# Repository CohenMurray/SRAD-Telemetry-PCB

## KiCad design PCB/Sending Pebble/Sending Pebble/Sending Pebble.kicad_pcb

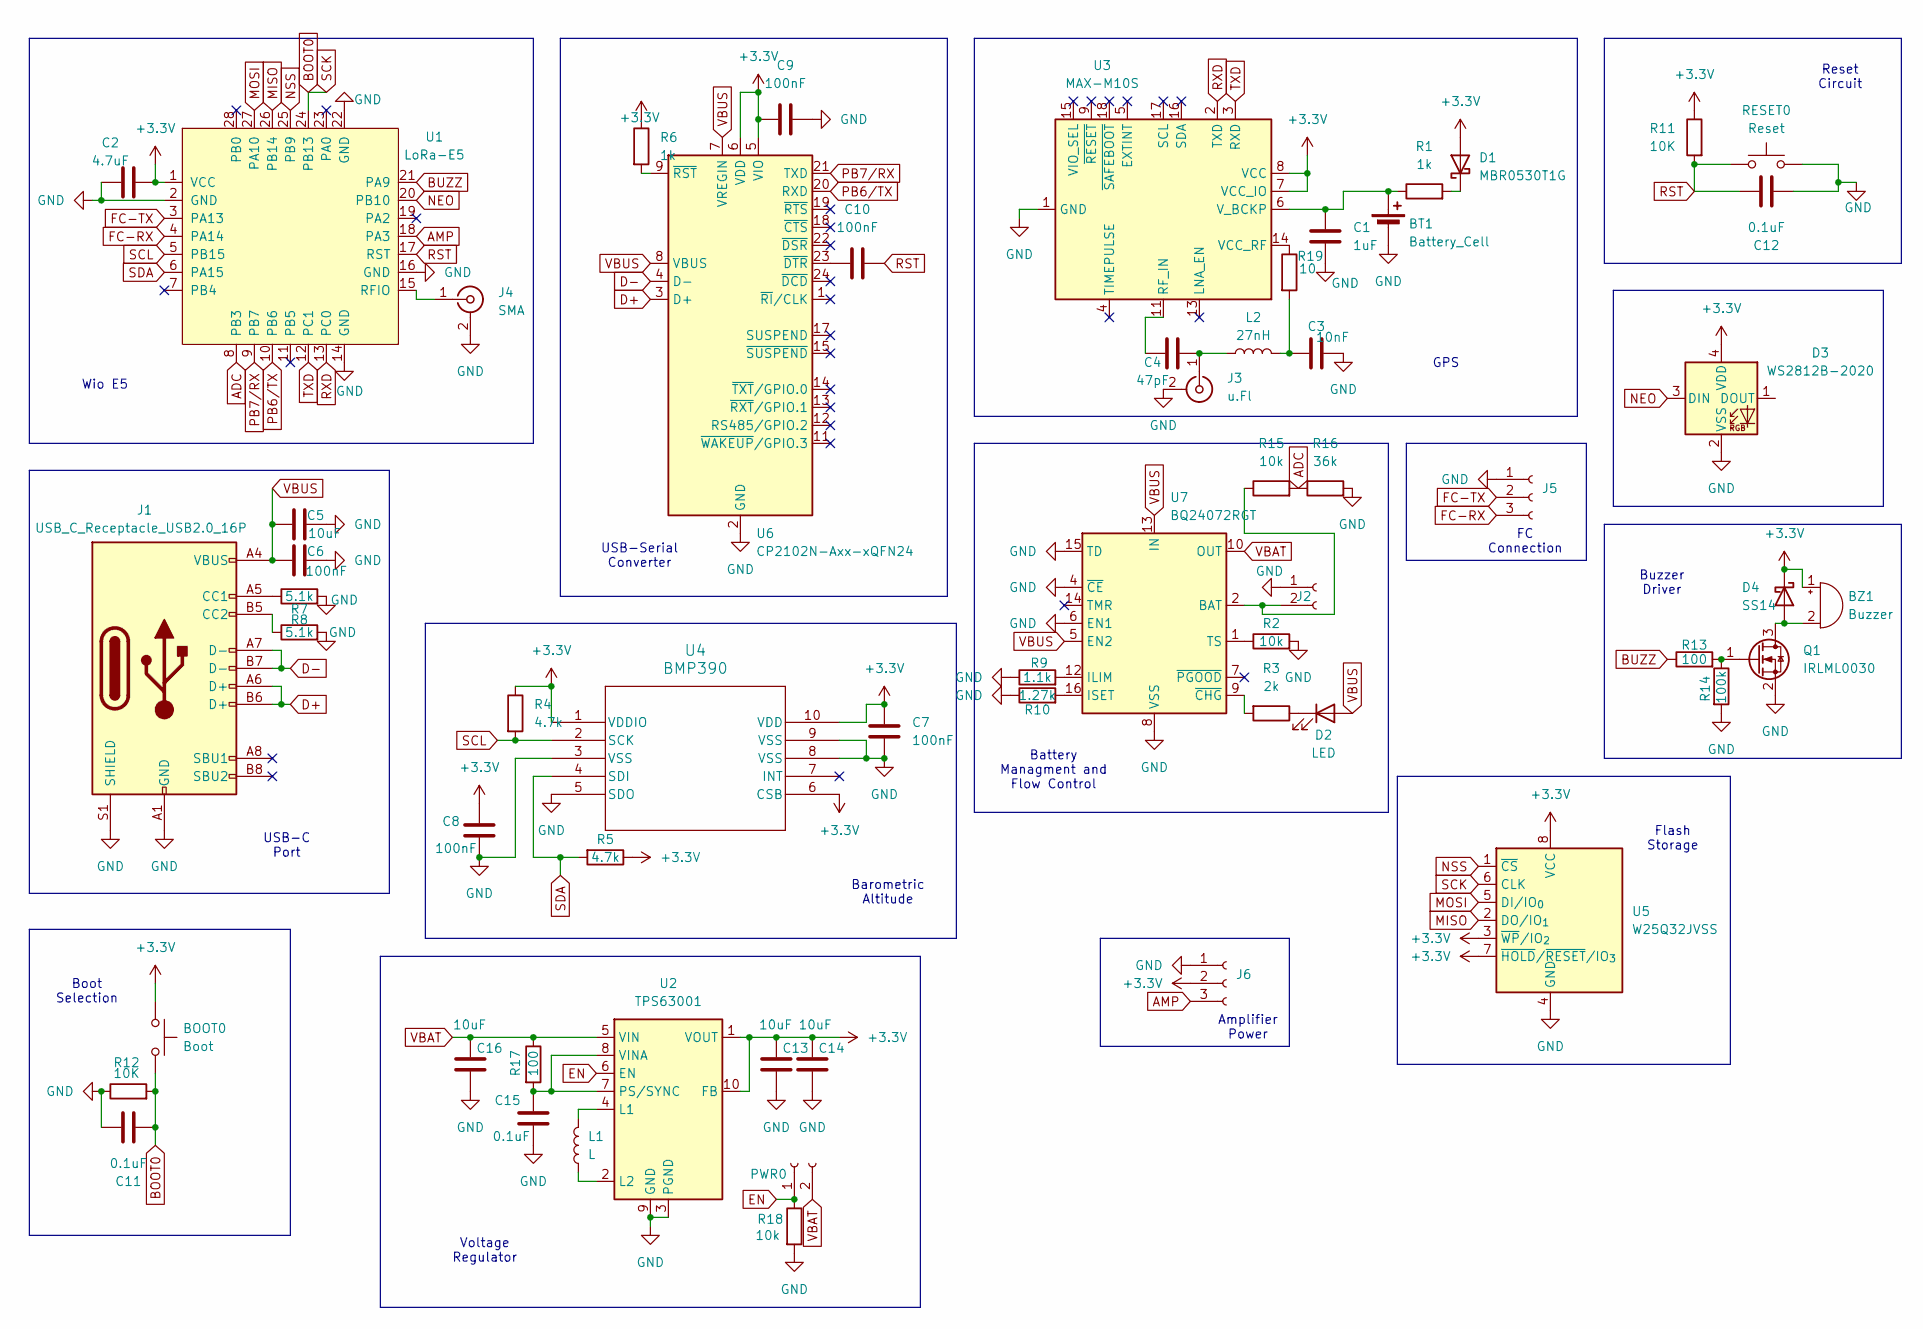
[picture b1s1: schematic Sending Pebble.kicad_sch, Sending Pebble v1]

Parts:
BOOT0: Boot; SW_SPST_PTS810
BT1: Battery_Cell; BatteryHolder_Seiko_MS621F
BZ1: Buzzer; MagneticBuzzer_PUI_SMT-1028-T-2-R
C1: 1uF; C_0603_1608Metric
C2: 4.7uF; C_0603_1608Metric
C3: 10nF; C_0402_1005Metric
C4: 47pF; C_0402_1005Metric
C5, C13, C14, C16: 10uF; C_0603_1608Metric
C6, C7, C8, C9, C10: 100nF; C_0603_1608Metric
C11, C12, C15: 0.1uF; C_0603_1608Metric
D1: MBR0530T1G; D_SOD-123
D2: LED; LED_0603_1608Metric
D3: WS2812B-2020; LED_WS2812B-2020_PLCC4_2.0x2.0mm
D4: SS14; D_SMA
J1: USB_C_Receptacle_USB2.0_16P; USB_C_Receptacle_HCTL_HC-TYPE-C-16P-01A
J2: Conn_01x02_Socket; JST_PH_S2B-PH-SM4-TB_1x02-1MP_P2.00mm_Horizontal
J3: u.Fl; U.FL_Hirose_U.FL-R-SMT-1_Vertical
J4: SMA; SMA_Amphenol_132289_EdgeMount
J5: Conn_01x03_Socket; JST_XH_B3B-XH-AM_1x03_P2.50mm_Vertical
J6: Conn_01x03_Socket; PinHeader_1x03_P2.54mm_Vertical
L1: L; IND_LQH3NPN2R2MMEL
L2: 27nH; C_0402_1005Metric
PWR0: Conn_01x02_Socket; PinSocket_1x02_P2.54mm_Vertical
Q1: IRLML0030; SOT-23
R1, R6: 1k; R_0603_1608Metric
R2, R15, R18: 10k; R_0603_1608Metric
R3: 2k; R_0603_1608Metric
R4, R5: 4.7k; R_0603_1608Metric
R7, R8: 5.1k; R_0603_1608Metric
R9: 1.1k; R_0603_1608Metric
R10: 1.27k; R_0603_1608Metric
R11, R12: 10K; R_0603_1608Metric
R13, R17: 100; R_0603_1608Metric
R14: 100k; R_0603_1608Metric
R16: 36k; R_0603_1608Metric
R19: 10; C_0402_1005Metric
RESET0: Reset; SW_SPST_PTS810
U1: LoRa-E5
U2: TPS63001; Texas_DRC0010J_ThermalVias
U3: MAX-M10S; ublox_MAX
U4: BMP390; 10LGA_2X2X0p75_BOS
U5: W25Q32JVSS; SOIC-8_5.3x5.3mm_P1.27mm
U6: CP2102N-Axx-xQFN24; QFN-24-1EP_4x4mm_P0.5mm_EP2.6x2.6mm
U7: BQ24072RGT; VQFN-16-1EP_3x3mm_P0.5mm_EP1.6x1.6mm

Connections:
+3.3V: BOOT0.1, BZ1.1 (+), C2.2, C7.1, C8.1, C9.1, C13.1, C14.1, D1.2 (A), D3.4 (VDD), D4.1 (K), J6.2, R4.1, R5.1, R6.1, R11.1, U1.1 (VCC), U2.1 (VOUT), U2.10 (FB), U3.7 (VCC_IO), U3.8 (VCC), U4.1 (VDDIO), U4.6 (CSB), U4.10 (VDD), U5.3 (~WP/IO_{2}), U5.7 (~HOLD/~RESET/IO_{3}), U5.8 (VCC), U6.5 (VIO), U6.6 (VDD)
ADC: R15.2, R16.1, U1.8 (PB3)
AMP: J6.3, U1.18 (PA3)
BOOT0: BOOT0.2, C11.2, R12.2, U1.24 (PB13~), U5.6 (CLK)
BUZZ: R13.1, U1.21 (PA9)
D+: J1.A6 (D+), J1.B6 (D+), U6.3 (D+)
D-: J1.A7 (D-), J1.B7 (D-), U6.4 (D-)
EN: PWR0.1, R18.1, U2.6 (EN)
FC-RX: J5.3, U1.4 (PA14)
FC-TX: J5.2, U1.3 (PA13)
GND: BT1.2 (-), C1.2, C2.1, C3.2, C5.2, C6.2, C7.2, C8.2, C9.2, C11.1, C12.2, C13.2, C14.2, C15.2, C16.2, D3.2 (VSS), J1.A1 (GND), J1.A12 (GND), J1.B1 (GND), J1.B12 (GND), J1.S1 (SHIELD), J2.1, J3.2 (Ext), J4.2 (Ext), J5.1, J6.1, Q1.2 (S), R2.2, R7.2, R8.2, R9.1, R10.1, R12.1, R14.2, R16.2, R18.2, RESET0.2, U1.2 (GND), U1.14 (GND), U1.16 (GND), U1.22 (GND), U2.3 (PGND), U2.9 (GND), U2.11 (PGND), U3.1 (GND), U3.10 (GND), U3.12 (GND), U4.3 (VSS), U4.5 (SDO), U4.8 (VSS), U4.9 (VSS), U5.4 (GND), U6.2 (GND), U6.25 (GND), U7.4 (~CE), U7.6 (EN1), U7.8 (VSS), U7.15 (TD), U7.17 (VSS)
MISO: U1.26 (PB14), U5.2 (DO/IO_{1})
MOSI: U1.27 (PA10), U5.5 (DI/IO_{0})
NEO: D3.3 (DIN), U1.20 (PB10)
NSS: U1.25 (PB9), U5.1 (~CS)
unnamed: BT1.1 (+), C1.1, R1.1, U3.6 (V_BCKP)
unnamed: BZ1.2 (-), D4.2 (A), Q1.3 (D)
unnamed: C3.1, L2.2, R19.2
unnamed: D1.1 (K), R1.2
unnamed: D2.1 (K), R3.1
unnamed: J1.A5 (CC1), R7.1
unnamed: J1.B5 (CC2), R8.1
unnamed: J2.2, R15.1, U7.2 (BAT), U7.3 (BAT)
unnamed: C4.2, J3.1 (In), L2.1
unnamed: J4.1 (In), U1.15 (RFIO)
unnamed: Q1.1 (G), R13.2, R14.1
unnamed: L1.2, U2.4 (L1)
unnamed: L1.1, U2.2 (L2)
unnamed: C15.1, R17.2, U2.7 (PS/SYNC), U2.8 (VINA)
unnamed: C4.1, U3.11 (RF_IN)
unnamed: R19.1, U3.14 (VCC_RF)
unnamed: C10.1, U6.23 (~DTR)
unnamed: R6.2, U6.9 (~RST)
unnamed: R9.2, U7.12 (ILIM)
unnamed: R10.2, U7.16 (ISET)
unnamed: R2.1, U7.1 (TS)
unnamed: R3.2, U7.9 (~CHG)
PB6/TX: U1.10 (PB6), U6.20 (RXD)
PB7/RX: U1.9 (PB7), U6.21 (TXD)
RST: C10.2, C12.1, R11.2, RESET0.1, U1.17 (RST)
RXD: U1.13 (PC0), U3.2 (TXD)
SCL: R4.2, U1.5 (PB15), U4.2 (SCK)
SDA: R5.2, U1.6 (PA15), U4.4 (SDI)
TXD: U1.12 (PC1), U3.3 (RXD)
VBAT: C16.1, PWR0.2, R17.1, U2.5 (VIN), U7.10 (OUT), U7.11 (OUT)
VBUS: C5.1, C6.1, D2.2 (A), J1.A4 (VBUS), J1.A9 (VBUS), J1.B4 (VBUS), J1.B9 (VBUS), U6.7 (VREGIN), U6.8 (VBUS), U7.5 (EN2), U7.13 (IN)

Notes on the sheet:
GPS
FC Connection
Battery Managment and Flow Control
USB-C Port
Flash Storage
Amplifier Power
Voltage Regulator
USB-Serial Converter
Barometric Altitude
Reset Circuit
Buzzer Driver
Wio E5
Boot Selection

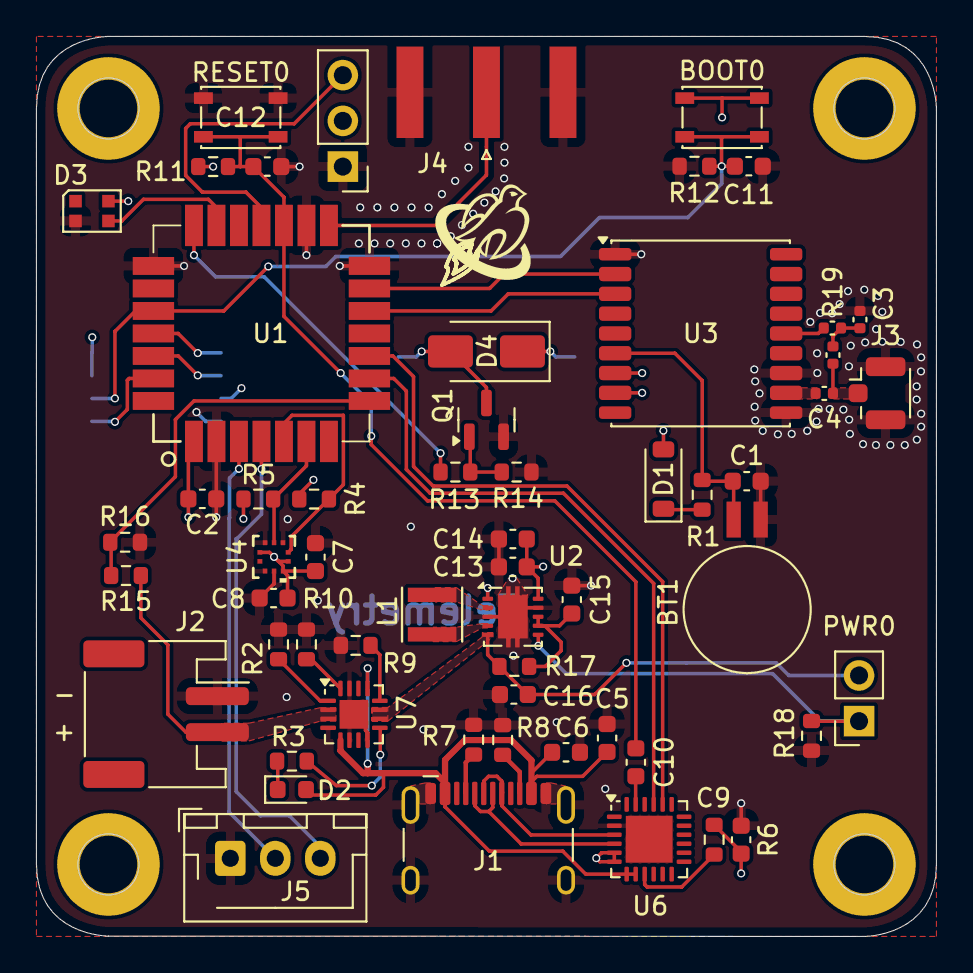
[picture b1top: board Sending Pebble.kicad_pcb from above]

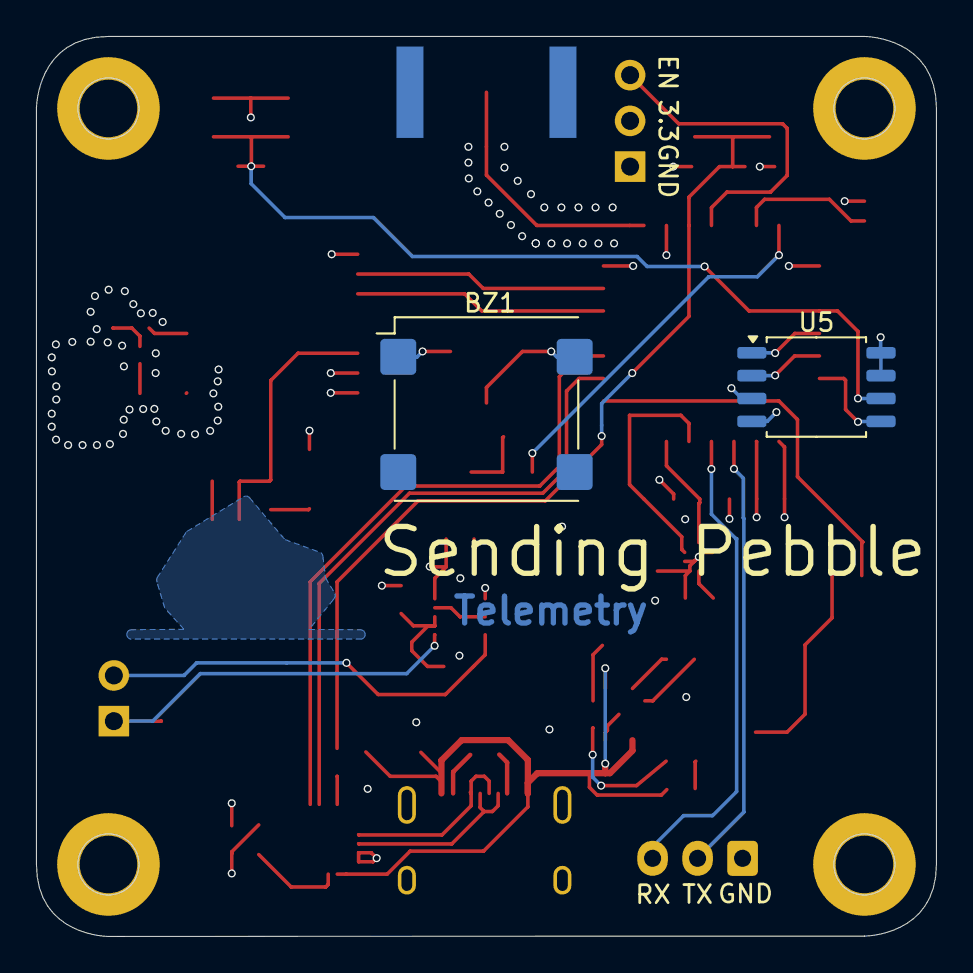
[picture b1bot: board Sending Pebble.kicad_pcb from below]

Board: 4 copper layers, 50.0 x 50.0 mm, 60 parts (2 on the bottom side), 46 nets.

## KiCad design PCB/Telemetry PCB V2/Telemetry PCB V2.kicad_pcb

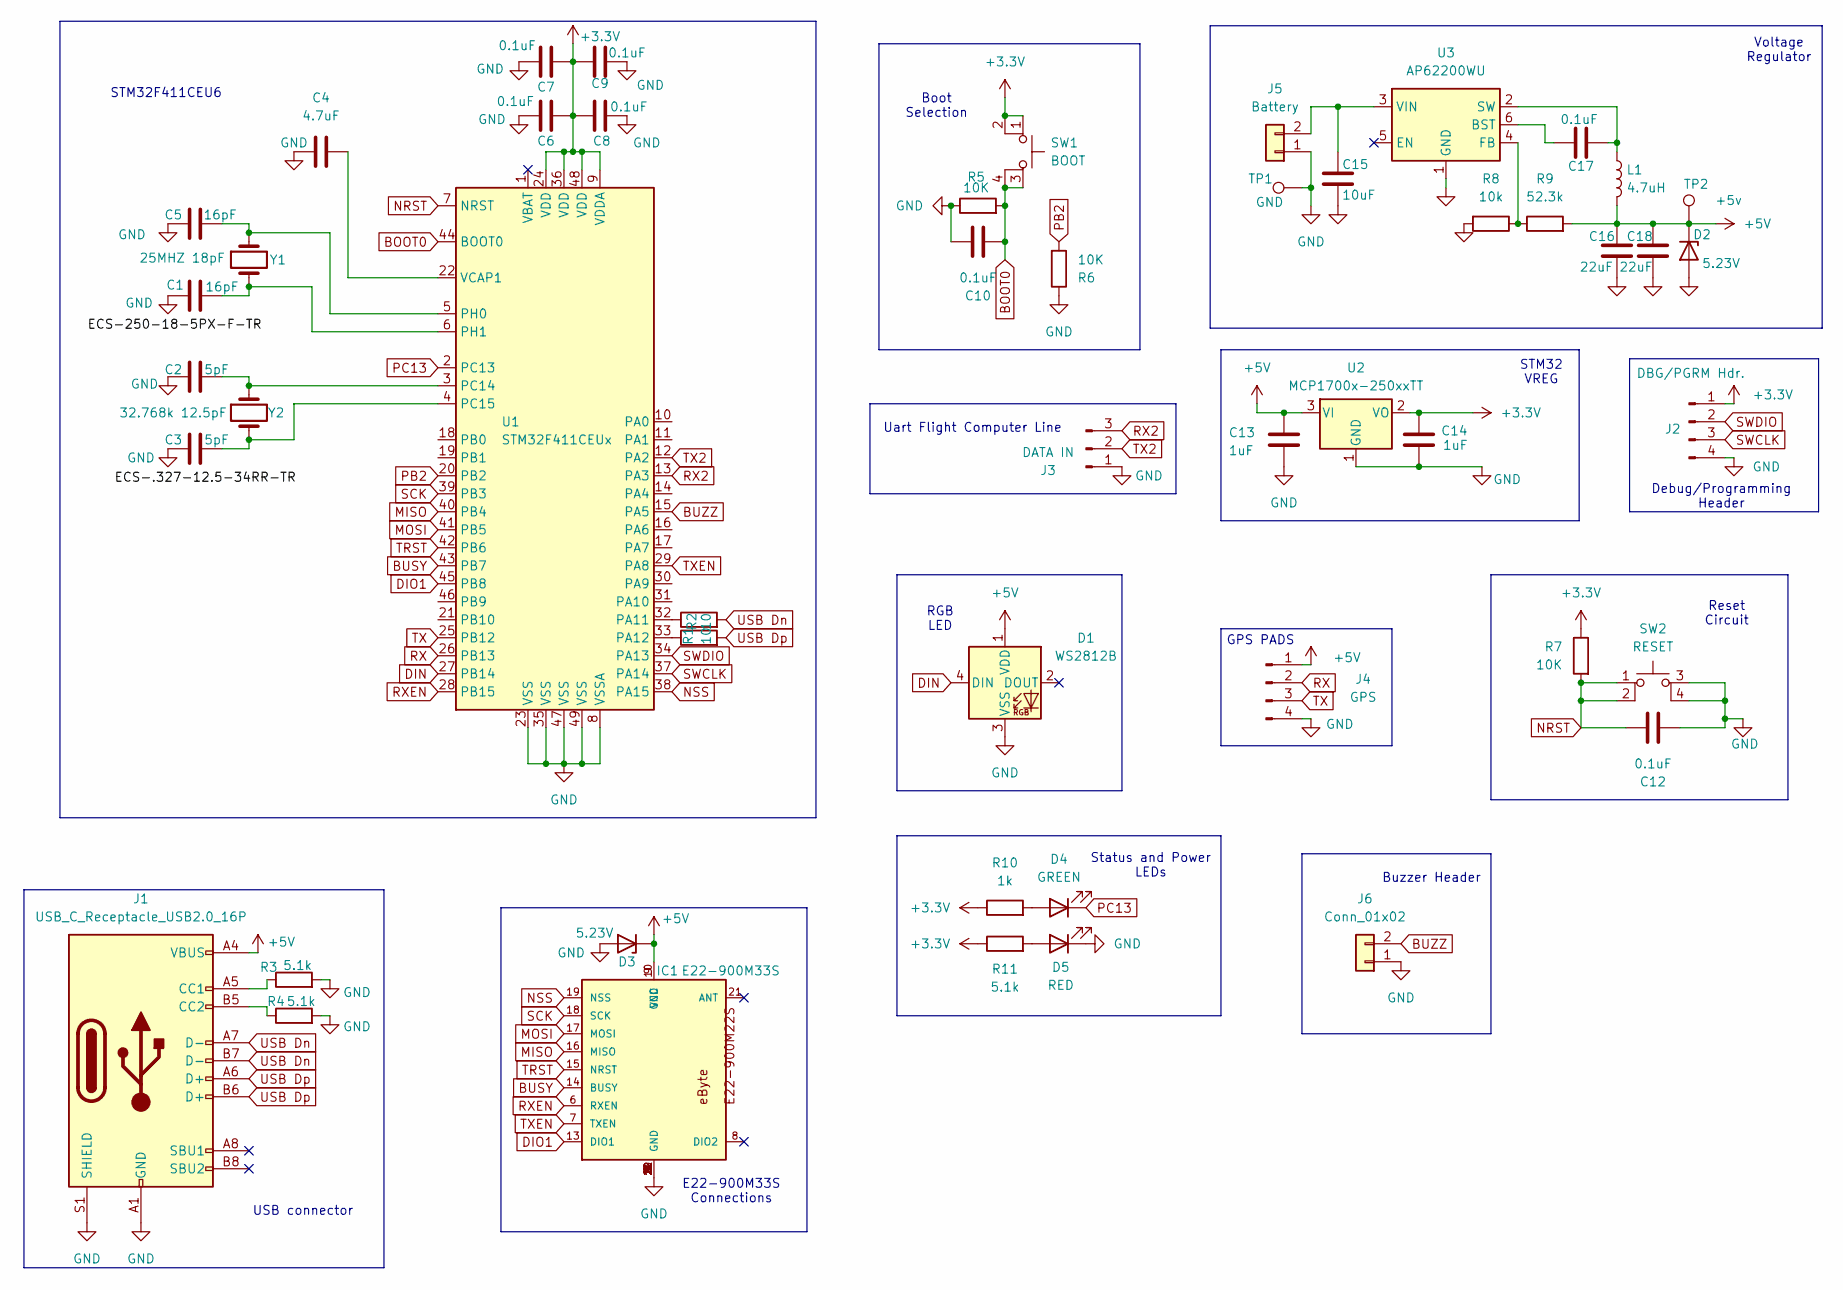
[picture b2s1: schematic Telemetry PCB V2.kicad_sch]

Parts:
C1, C5: 16pF; C_1206_3216Metric_Pad1.33x1.80mm_HandSolder
C2, C3: 5pF; C_0603_1608Metric_Pad1.08x0.95mm_HandSolder
C4: 4.7uF; C_1206_3216Metric_Pad1.33x1.80mm_HandSolder
C6, C7, C8, C9: 0.1uF; C_0603_1608Metric_Pad1.08x0.95mm_HandSolder
C10, C12, C17: 0.1uF; C_1206_3216Metric_Pad1.33x1.80mm_HandSolder
C13, C14: 1uF; C_1206_3216Metric_Pad1.33x1.80mm_HandSolder
C15: 10uF; C_1206_3216Metric_Pad1.33x1.80mm_HandSolder
C16, C18: 22uF; C_1206_3216Metric_Pad1.33x1.80mm_HandSolder
D1: WS2812B; LED_WS2812B_PLCC4_5.0x5.0mm_P3.2mm
D2, D3: 5.23V; CR_1C-G3&slash_H_VIS
D4: GREEN; LED_1206_3216Metric
D5: RED; LED_1206_3216Metric
IC1: E22-900M33S; XCVR_E22-900M33S
J1: USB_C_Receptacle_USB2.0_16P; USB_C_Receptacle_HCTL_HC-TYPE-C-16P-01A (SMALLER PADS)
J2: DBG/PGRM Hdr.; PinHeader_1x04_P2.54mm_Vertical
J3: DATA IN; JST_XH_B3B-XH-A_1x03_P2.50mm_Vertical
J4: GPS; PinHeader_1x04_P2.54mm_Vertical
J5: Battery; JST_XH_B2B-XH-A_1x02_P2.50mm_Vertical
J6: Conn_01x02; JST_XH_B2B-XH-A_1x02_P2.50mm_Vertical
L1: 4.7uH; IND_SRN5040_BRN
R1, R2: 10; C_1206_3216Metric_Pad1.33x1.80mm_HandSolder
R3, R4: 5.1k; C_1206_3216Metric_Pad1.33x1.80mm_HandSolder
R5, R6, R7: 10K; R_1206_3216Metric_Pad1.30x1.75mm_HandSolder
R8: 10k; R_1206_3216Metric_Pad1.30x1.75mm_HandSolder
R9: 52.3k; R_1206_3216Metric_Pad1.30x1.75mm_HandSolder
R10: 1k; R_1206_3216Metric
R11: 5.1k; R_1206_3216Metric
SW1: BOOT; SON4_PTS526 SM15 SMTR2 LFS_CNK
SW2: RESET; SON4_PTS526 SM15 SMTR2 LFS_CNK
TP1: GND; TestPoint_Loop_D1.80mm_Drill1.0mm_Beaded
TP2: +5v; TestPoint_Loop_D1.80mm_Drill1.0mm_Beaded
U1: STM32F411CEUx; QFN-48-1EP_7x7mm_P0.5mm_EP5.6x5.6mm
U2: MCP1700x-250xxTT; SOT-23
U3: AP62200WU; TSOT-23-6
Y1: 25MHZ 18pF; Crystal_SMD_HC49-SD_HandSoldering
Y2: 32.768k 12.5pF; XTAL_ECS-.327-12.5-34RR-TR

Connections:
+3.3V: C6.2, C7.1, C8.1, C9.2, C14.1, J2.1, R7.1, R10.1, R11.1, SW1.1, SW1.2, U1.9 (VDDA), U1.24 (VDD), U1.36 (VDD), U1.48 (VDD), U2.2 (VO)
+5V: C13.1, C16.2, C18.2, D1.1 (VDD), D2.1 (K), D3.1 (K), IC1.9 (VCC), IC1.10 (GND), J1.A4 (VBUS), J1.A9 (VBUS), J1.B4 (VBUS), J1.B9 (VBUS), J4.1, L1.2, R9.2, TP2.1, U2.3 (VI)
BOOT0: C10.2, R5.2, SW1.3 (A), SW1.4 (K), U1.44 (BOOT0)
BUSY: IC1.14 (BUSY), U1.43 (PB7)
BUZZ: J6.2, U1.15 (PA5)
DIN: D1.4 (DIN), U1.27 (PB14)
DIO1: IC1.13 (DIO1), U1.45 (PB8)
GND: C1.1, C2.1, C3.2, C4.1, C5.1, C6.1, C7.2, C8.2, C9.1, C10.1, C12.2, C13.2, C14.2, C15.2, C16.1, C18.1, D1.3 (VSS), D2.2 (A), D3.2 (A), D5.1 (K), IC1.1 (GND), IC1.2 (GND), IC1.3 (GND), IC1.4 (GND), IC1.5 (GND), IC1.11 (GND), IC1.12 (GND), IC1.20 (GND), IC1.22 (GND), J1.A1 (GND), J1.A12 (GND), J1.B1 (GND), J1.B12 (GND), J1.S1 (SHIELD), J2.4, J3.1, J4.4, J5.1, J6.1, R3.2, R4.2, R5.1, R6.1, R8.2, SW2.3 (A), SW2.4 (K), TP1.1, U1.8 (VSSA), U1.23 (VSS), U1.35 (VSS), U1.47 (VSS), U1.49 (VSS), U2.1 (GND), U3.1 (GND)
MISO: IC1.16 (MISO), U1.40 (PB4)
MOSI: IC1.17 (MOSI), U1.41 (PB5)
NRST: C12.1, R7.2, SW2.1, SW2.2, U1.7 (NRST)
NSS: IC1.19 (NSS), U1.38 (PA15)
unnamed: D4.2 (A), R10.2
unnamed: D5.2 (A), R11.2
unnamed: J1.A5 (CC1), R3.1
unnamed: J1.B5 (CC2), R4.1
unnamed: C15.1, J5.2, U3.3 (VIN)
unnamed: R1.1, U1.32 (PA11)
unnamed: R2.1, U1.33 (PA12)
unnamed: C2.2, U1.3 (PC14), Y2.1
unnamed: C3.1, U1.4 (PC15), Y2.2
unnamed: C5.2, U1.5 (PH0), Y1.1
unnamed: C1.2, U1.6 (PH1), Y1.2
unnamed: C4.2, U1.22 (VCAP1)
unnamed: C17.1, U3.6 (BST)
unnamed: R8.1, R9.1, U3.4 (FB)
unnamed: C17.2, L1.1, U3.2 (SW)
PB2: R6.2, U1.20 (PB2)
PC13: D4.1 (K), U1.2 (PC13)
RX: J4.2, U1.26 (PB13)
RX2: J3.3, U1.13 (PA3)
RXEN: IC1.6 (RXEN), U1.28 (PB15)
SCK: IC1.18 (SCK), U1.39 (PB3)
SWCLK: J2.3, U1.37 (PA14)
SWDIO: J2.2, U1.34 (PA13)
TRST: IC1.15 (NRST), U1.42 (PB6)
TX: J4.3, U1.25 (PB12)
TX2: J3.2, U1.12 (PA2)
TXEN: IC1.7 (TXEN), U1.29 (PA8)
USB Dn: J1.A7 (D-), J1.B7 (D-), R1.2
USB Dp: J1.A6 (D+), J1.B6 (D+), R2.2

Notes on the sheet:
Boot Selection
Reset Circuit
GPS PADS
STM32 VREG
E22-900M33S Connections
Debug/Programming Header
Buzzer Header
Status and Power LEDs
USB connector
Uart Flight Computer Line
Voltage Regulator
STM32F411CEU6
RGB LED

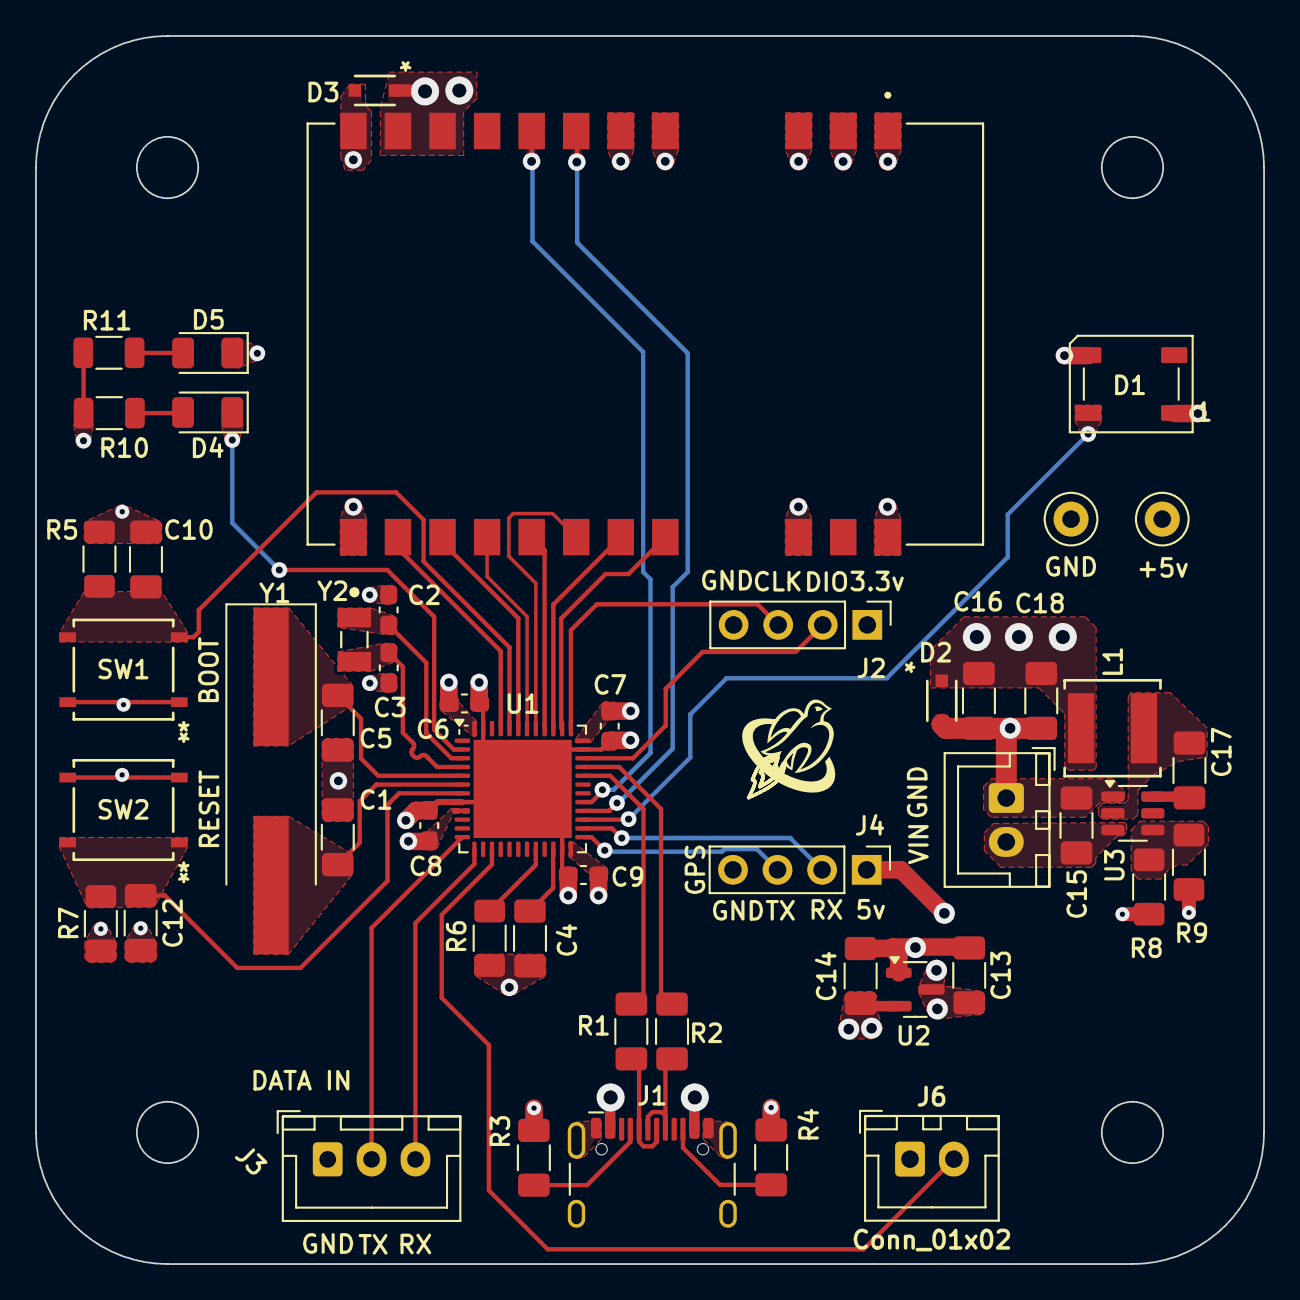
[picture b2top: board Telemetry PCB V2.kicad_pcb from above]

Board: 4 copper layers, 70.0 x 70.0 mm, 50 parts (0 on the bottom side), 41 nets.

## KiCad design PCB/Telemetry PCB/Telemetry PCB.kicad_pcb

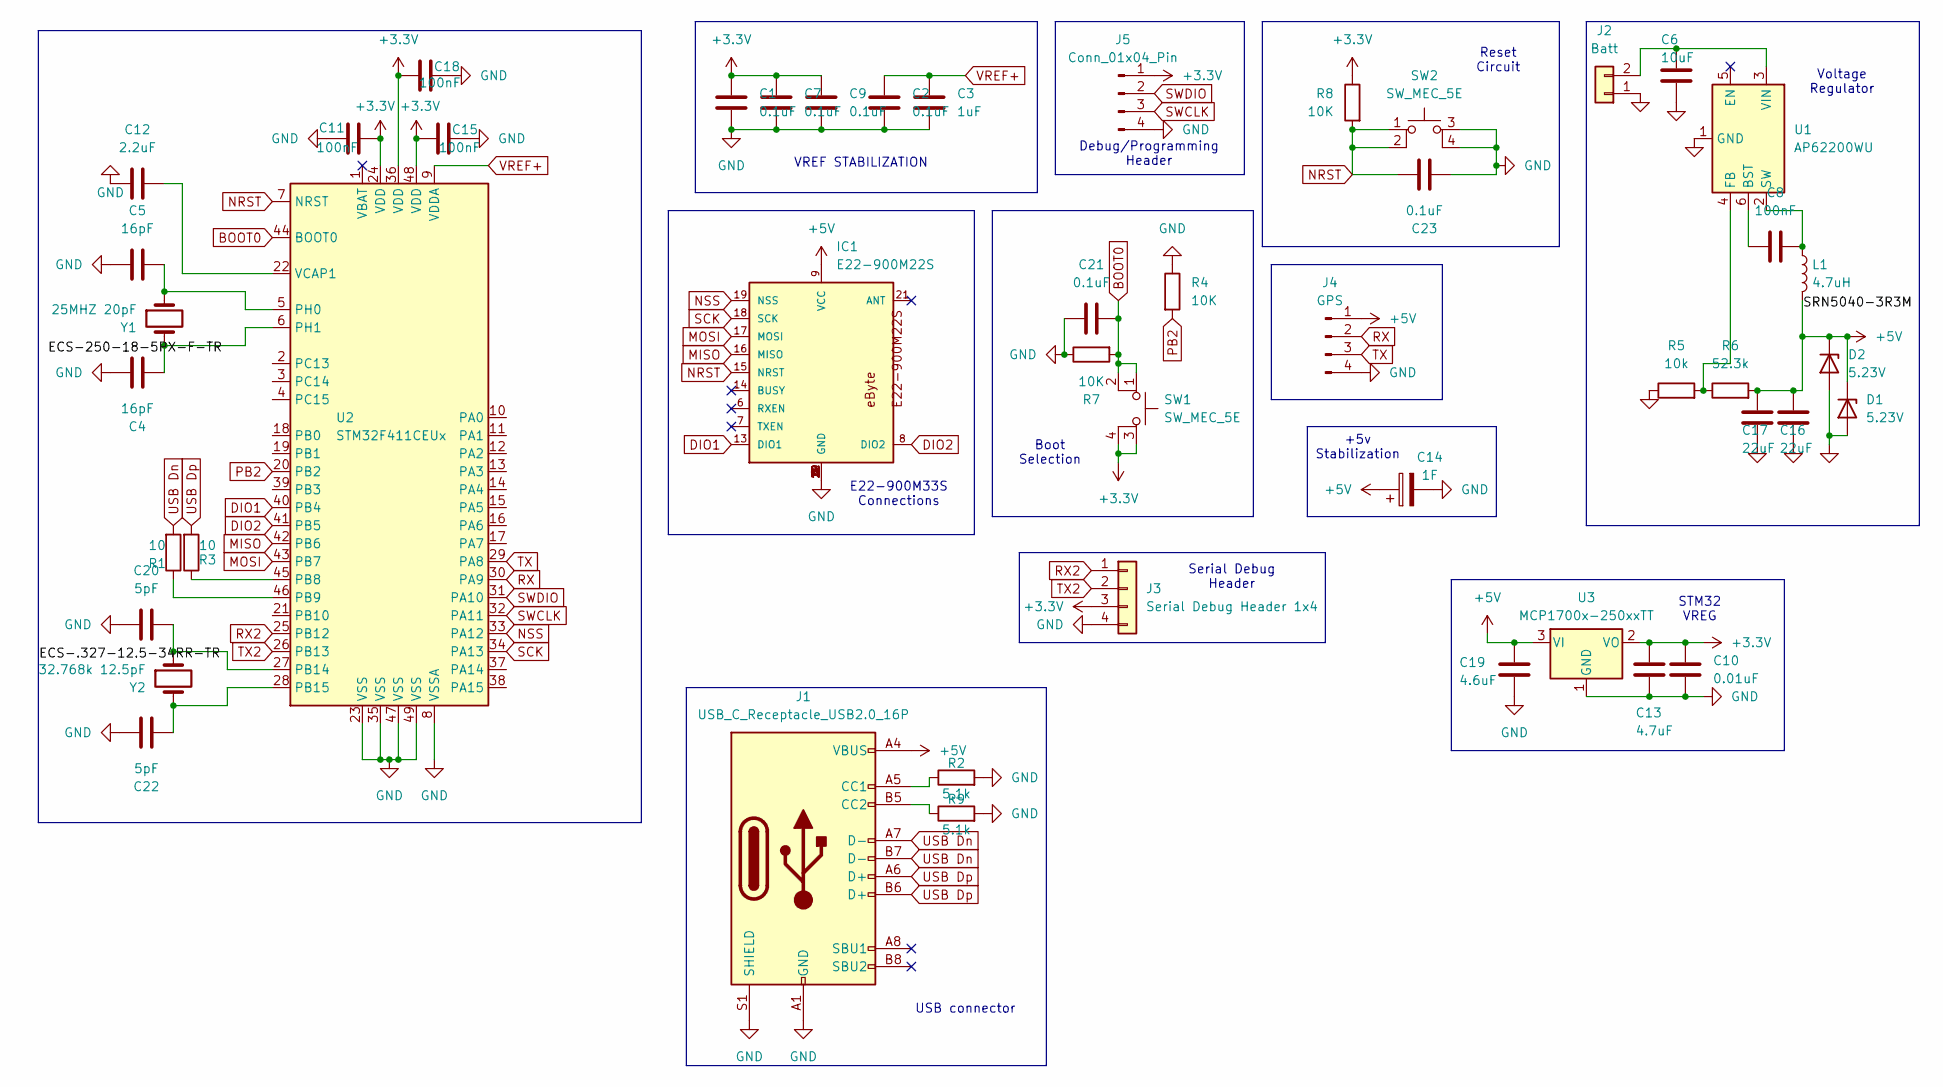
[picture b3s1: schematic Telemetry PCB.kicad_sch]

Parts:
C1, C2, C7, C9, C21, C23: 0.1uF; C_1206_3216Metric_Pad1.33x1.80mm_HandSolder
C3: 1uF; C_1206_3216Metric_Pad1.33x1.80mm_HandSolder
C4, C5: 16pF; C_1206_3216Metric_Pad1.33x1.80mm_HandSolder
C6: 10uF; C_1206_3216Metric_Pad1.33x1.80mm_HandSolder
C8, C11, C15, C18: 100nF; C_1206_3216Metric_Pad1.33x1.80mm_HandSolder
C10: 0.01uF; C_1206_3216Metric_Pad1.33x1.80mm_HandSolder
C12: 2.2uF; C_1206_3216Metric_Pad1.33x1.80mm_HandSolder
C13: 4.7uF; C_1206_3216Metric_Pad1.33x1.80mm_HandSolder
C14: 1F; C_Radial_D10.0mm_H20.0mm_P5.00mm
C16, C17: 22uF; C_1206_3216Metric_Pad1.33x1.80mm_HandSolder
C19: 4.6uF; C_1206_3216Metric_Pad1.33x1.80mm_HandSolder
C20, C22: 5pF; C_1206_3216Metric_Pad1.33x1.80mm_HandSolder
D1, D2: 5.23V; CR_1C-G3&slash_H_VIS
IC1: E22-900M22S; XCVR_E22-900M30S
J1: USB_C_Receptacle_USB2.0_16P; USB_C_Receptacle_GCT_USB4105-xx-A_16P_TopMnt_Horizontal
J2: Batt; PinHeader_1x02_P2.54mm_Vertical
J3: Serial Debug Header 1x4; PinHeader_1x04_P2.54mm_Vertical
J4: GPS; PinHeader_1x04_P2.54mm_Vertical
J5: Conn_01x04_Pin; PinHeader_1x04_P2.54mm_Vertical
L1: 4.7uH; IND_SRN5040_BRN
R1, R3: 10; C_1206_3216Metric_Pad1.33x1.80mm_HandSolder
R2, R9: 5.1k; C_1206_3216Metric_Pad1.33x1.80mm_HandSolder
R4, R7, R8: 10K; R_1206_3216Metric_Pad1.30x1.75mm_HandSolder
R5: 10k; R_1206_3216Metric_Pad1.30x1.75mm_HandSolder
R6: 52.3k; R_1206_3216Metric_Pad1.30x1.75mm_HandSolder
SW1, SW2: SW_MEC_5E; SON4_PTS526 SM15 SMTR2 LFS_CNK
U1: AP62200WU; TSOT-23-6
U2: STM32F411CEUx; QFN-48-1EP_7x7mm_P0.5mm_EP5.6x5.6mm
U3: MCP1700x-250xxTT; SOT-23
Y1: 25MHZ 20pF; Crystal_SMD_HC49-SD_HandSoldering
Y2: 32.768k 12.5pF; XTAL_ECS-.327-12.5-34RR-TR

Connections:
+3.3V: C1.1, C7.1, C9.1, C10.1, C11.2, C13.1, C15.1, C18.1, J3.3, J5.1, R8.1, SW1.3 (A), SW1.4 (K), U2.24 (VDD), U2.36 (VDD), U2.48 (VDD), U3.2 (VO)
+5V: C14.1, C16.2, C17.2, C19.1, D1.1 (K), D2.1 (K), IC1.9 (VCC), J1.A4 (VBUS), J1.A9 (VBUS), J1.B4 (VBUS), J1.B9 (VBUS), J4.1, L1.2, R6.2, U3.3 (VI)
BOOT0: C21.2, R7.2, SW1.1, SW1.2, U2.44 (BOOT0)
DIO1: IC1.13 (DIO1), U2.40 (PB4)
DIO2: IC1.8 (DIO2), U2.41 (PB5)
GND: C1.2, C2.2, C3.2, C4.1, C5.1, C6.2, C7.2, C9.2, C10.2, C11.1, C12.1, C13.2, C14.2, C15.2, C16.1, C17.1, C18.2, C19.2, C20.1, C21.1, C22.2, C23.2, D1.2 (A), D2.2 (A), IC1.1 (GND), IC1.2 (GND), IC1.3 (GND), IC1.4 (GND), IC1.5 (GND), IC1.10 (GND), IC1.11 (GND), IC1.12 (GND), IC1.20 (GND), IC1.22 (GND), J1.A1 (GND), J1.A12 (GND), J1.B1 (GND), J1.B12 (GND), J1.S1 (SHIELD), J2.1, J3.4, J4.4, J5.4, R2.2, R4.1, R5.1, R7.1, R9.2, SW2.3 (A), SW2.4 (K), U1.1 (GND), U2.8 (VSSA), U2.23 (VSS), U2.35 (VSS), U2.47 (VSS), U2.49 (VSS), U3.1 (GND)
MISO: IC1.16 (MISO), U2.42 (PB6)
MOSI: IC1.17 (MOSI), U2.43 (PB7)
NRST: C23.1, IC1.15 (NRST), R8.2, SW2.1, SW2.2, U2.7 (NRST)
NSS: IC1.19 (NSS), U2.33 (PA12)
unnamed: J1.A5 (CC1), R2.1
unnamed: J1.B5 (CC2), R9.1
unnamed: C6.1, J2.2, U1.3 (VIN)
unnamed: C8.1, U1.6 (BST)
unnamed: R5.2, R6.1, U1.4 (FB)
unnamed: C8.2, L1.1, U1.2 (SW)
unnamed: R3.1, U2.45 (PB8)
unnamed: R1.1, U2.46 (PB9)
unnamed: C20.2, U2.27 (PB14), Y2.1
unnamed: C22.1, U2.28 (PB15), Y2.2
unnamed: C5.2, U2.5 (PH0), Y1.1
unnamed: C4.2, U2.6 (PH1), Y1.2
unnamed: C12.2, U2.22 (VCAP1)
PB2: R4.2, U2.20 (PB2)
RX: J4.2, U2.30 (PA9)
RX2: J3.1, U2.25 (PB12)
SCK: IC1.18 (SCK), U2.34 (PA13)
SWCLK: J5.3, U2.32 (PA11)
SWDIO: J5.2, U2.31 (PA10)
TX: J4.3, U2.29 (PA8)
TX2: J3.2, U2.26 (PB13)
USB Dn: J1.A7 (D-), J1.B7 (D-), R1.2
USB Dp: J1.A6 (D+), J1.B6 (D+), R3.2
VREF+: C2.1, C3.1, U2.9 (VDDA)

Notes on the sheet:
Boot Selection
Reset Circuit
STM32 VREG
E22-900M33S Connections
Debug/Programming Header
USB connector
VREF STABILIZATION
Serial Debug Header
Voltage Regulator
+5v Stabilization

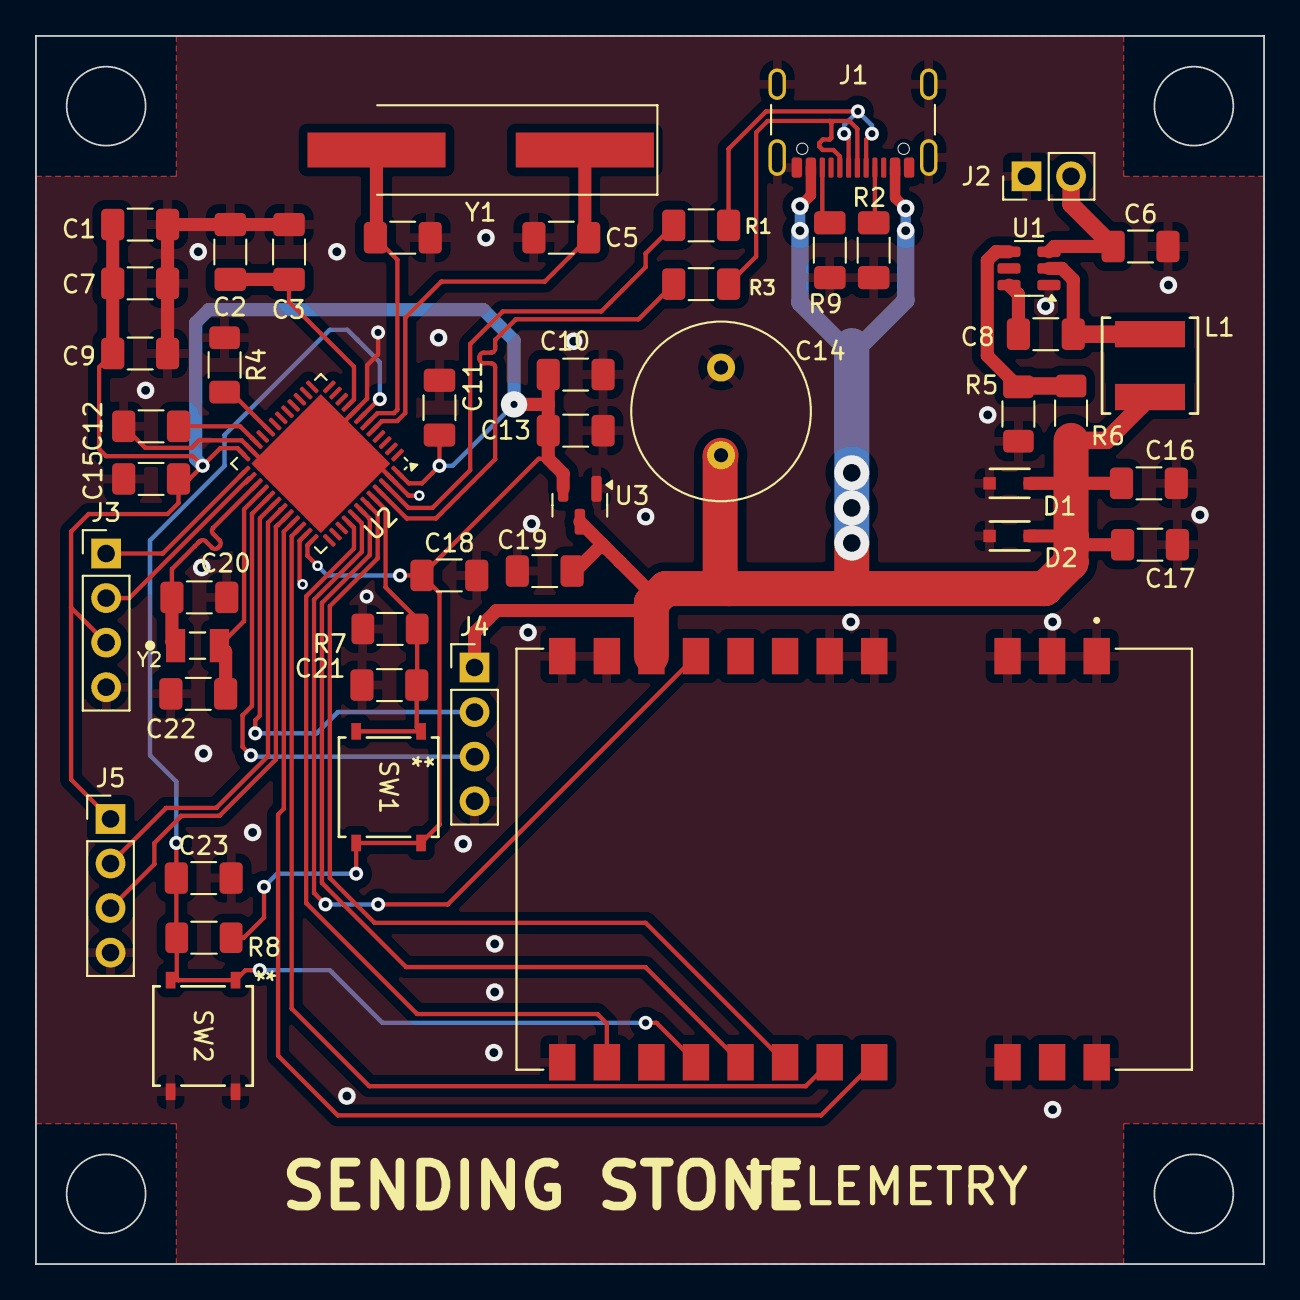
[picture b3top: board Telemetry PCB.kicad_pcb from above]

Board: 2 copper layers, 70.0 x 70.0 mm, 48 parts (0 on the bottom side), 34 nets.

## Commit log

2024-10-24 Initial document creation and schematic start
2024-10-25 Boot, reset and VREF circuits and programming header added
2024-10-25 E22-900M33s initial circuitry added
2024-10-26 Added gps connection
2024-10-28 Update e22-900m33s library and add gps connection to mcu
    e22-900m33s had wrong footprint library. Library has been updated to proper one.
2024-10-31 Added buck converter circuit
2024-10-31 Rewired vreg circuit
2024-11-01 removed potentiometer and replaced with exact value resistors
2024-11-02 added component values for vreg
2024-11-07 added footprints
2024-11-07 more footprints
2024-11-07 changed switching regulator to 5v added 3.3v linear regulator
2024-11-09 Added usb & footprints. Tweaked Crystals
    Changed Crystals and associated caps
    duplicated Zener diode
    added usb connection (moved dio1 & dio2 from PA11 & 12 to PB8 & 9)
    added footprints to all components
2024-11-11 see last push discription
    Last push did not work. see last push for description
2024-11-12 First Board Prototype
    tweaked the filter caps for stm32. changed switches. and moved many pins around on the stm32 to ease trace routing. Created first board prototype
2024-11-12 Updated silkscreen and fixed front plane islands
    Updated silkscreen and fixed front plane islands
2024-11-12 reannotated based on board geometry
    reannotated based on board geometry
2024-11-14 Added missing Gnd trace on Stm32
    Added missing Gnd trace on Stm32
2024-11-17 Tweaked usb and data traces
    Tweaked usb board should be able to be powered by usb without catching fire
    I also moved some data traces away from each other and filled between them to lower their parasitic capacitance
2024-11-24 Updated E22 connections
2024-12-20 Started work on SRAD Prototype V2
    Moved to a 4 layer PCB.
    Changed the value of the filter capacitors near the linear voltage regulator to better fit our use case.
    moved some of the IO pins around for routing reasons.
2024-12-30 Continued Layout for V2
    Continued to place components and layout for v2 board.
2025-01-09 continued work on v2
    Placed many polygon pads and moved various components around
2025-01-09 Work continues
    More pads + tinkered with Vias. Also reoriented the 32kHz crystal so that the load capacitors were between it and the MCU.
2025-01-19 changed power connector
    Changed power connector to JST-XH 2pin and moved some stuff a tiny bit
2025-01-19 closed file to prevent warning message
    closed file to prevent warning message
2025-01-19 added bolt clearance, moved switches
    added bolt clearance sections. I also moved the nrst switch because it has to connect to the transmitter and because its previous location was in the bolt clearance zone.
2025-01-19 corrected washer size
2025-01-19 Corrected spi and uart connections
2025-01-19 Pins that were wrong are now right
    Pins that were wrong are now right and also changed form 1206 capacitors to 0603 capacitors for the load capacitors on the low speed oscillator to reduce size for placement reasons.
2025-01-20 much progress
    Added power planes, edge cuts, and connected many components
2025-01-20 minor placement tweaks
2025-01-22 All connections made
    All components are now connected all the remains is tweaking a few connections that violate clearances and making the silk screen legible.
2025-01-22 minor fill tweaks
2025-01-24 Zero Errors, silkscreen warnings
    Zero errors remain all connections are made and within clearance. remaining warnings are about footprint libraries and silkscreen.
2025-01-25 tweaked mounting holes
    Ensured mounting holes were concentric with filled zones and correct distance from the edge. also added dimensions
2025-01-25 Changed lines around holes to ruled zones
    the lines that were used to prevent fills were becoming traces so I changed them to rule zones that prevent anything from entering the zone
2025-01-27 Updated .gitignore to ignore backups folder
2025-01-28 changed many things
    changed capacitor footprint, moved tx2 and rx2 to a uart pin. moved nrst switch moved j3 header
2025-02-01 Revamped power, made usb better
    Revamped the layout of the voltage regulator to match closer to the recommend layout form the data sheet.
    Realized I didn't need vias for the usb lines so they are much nicer now
2025-02-21 Large Board Update
    Changed stack-up order to signal-ground-power-signal2
    tweaked constraints for vias and spacing then adjusted components to fit
    changed stm decoupling capacitors to smaller better placed footprints.
2025-02-22 Broad tweaks
    Tweaked the location of many power components by small amounts.
    Changed to two 1000uF capacitors foe smoothing
    swapped Flight computer pin header to 3 pin jst-xh
2025-02-22 added test points
2025-02-23 :D
    board is done as best I can tell
    This update fully removed the smoothing caps as experienced people don't believe they are necessary. This resulted in moving a couple components around.
    The vias greater than 0.5mm have had solder mask free zones added on them to prevent JLC from trying plug them because JLC says that plugging is likely to fail on large vias.
2025-03-02 Changed GPS power to 5V
    Changed GPS power to 5V because I was not sure what it's current draw is and we don't have a ton of spare capacity on the 3.3V power regulator. Powering of of 5V is also likely more power efficient a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
2025-03-07 Production files generated
    one via and a single silkscreen tweaked to fit jlcpcb rules. All production files generated following jlcpcb guidelines
2025-03-07 Created Production Files.zip
2025-06-09 Changed schematic to reflect issues found, started to modify board layout.
2025-06-10 Finished updating board to reflect issues and new components
2025-06-10 Started adding labels
2025-06-11 Finished adding labels, fixed DRC violations
2025-06-11 Changed gitignore to include more files
2025-06-13 Moved some components
2025-06-13 Fixed Fill Zones
2025-06-20 Generated Gerber files
    Generated Gerber files and drill files and drill map
2025-07-08 Version 2.1
    This Is the second board revision and the one that will be launched at LC 2025
    There is an incorrect Pinout for the transmitter module It has been clearly marked on the Fab layer
    The Boards have been modified after manufacturing.
2025-07-08 V 2.2 Updated Incorrect Pinout
    The Transmitter pinout has been corrected.
    Disregard previous message this will be The flight revision of the board.
2025-07-13 Moved Debug Header Slightly
    Moved Debug Header Slightly to accommodate buzzer better
2025-07-21 added JLCPCB config picture
2025-07-21 Added buzzer header
2025-07-25 Added Graphics
2025-07-25 Generated production files
2025-08-26 Initial Sending Pebble Commit and Schematic V1
2025-08-26 Finished Footprint Assignment
2025-08-27 Started Layout, Added DRC
2025-08-28 Power Circuitry almost finished
2025-08-31 Updated DRC Rules
2025-08-31 Finalized form factor, added coplanar waveguides for feedlines and placed all components on board
2025-08-31 More layout and trace routing
2025-09-01 Fixed VREG type, more routing
2025-09-02 More routing, added FC connection
2025-09-19 More routing, added amplifier connector, fixed coplanar waveguide. Started adding graphics
2025-09-22 Finished RF design, added finished graphics, added pin labels
2025-10-25 Final Changes, Fab files generated
